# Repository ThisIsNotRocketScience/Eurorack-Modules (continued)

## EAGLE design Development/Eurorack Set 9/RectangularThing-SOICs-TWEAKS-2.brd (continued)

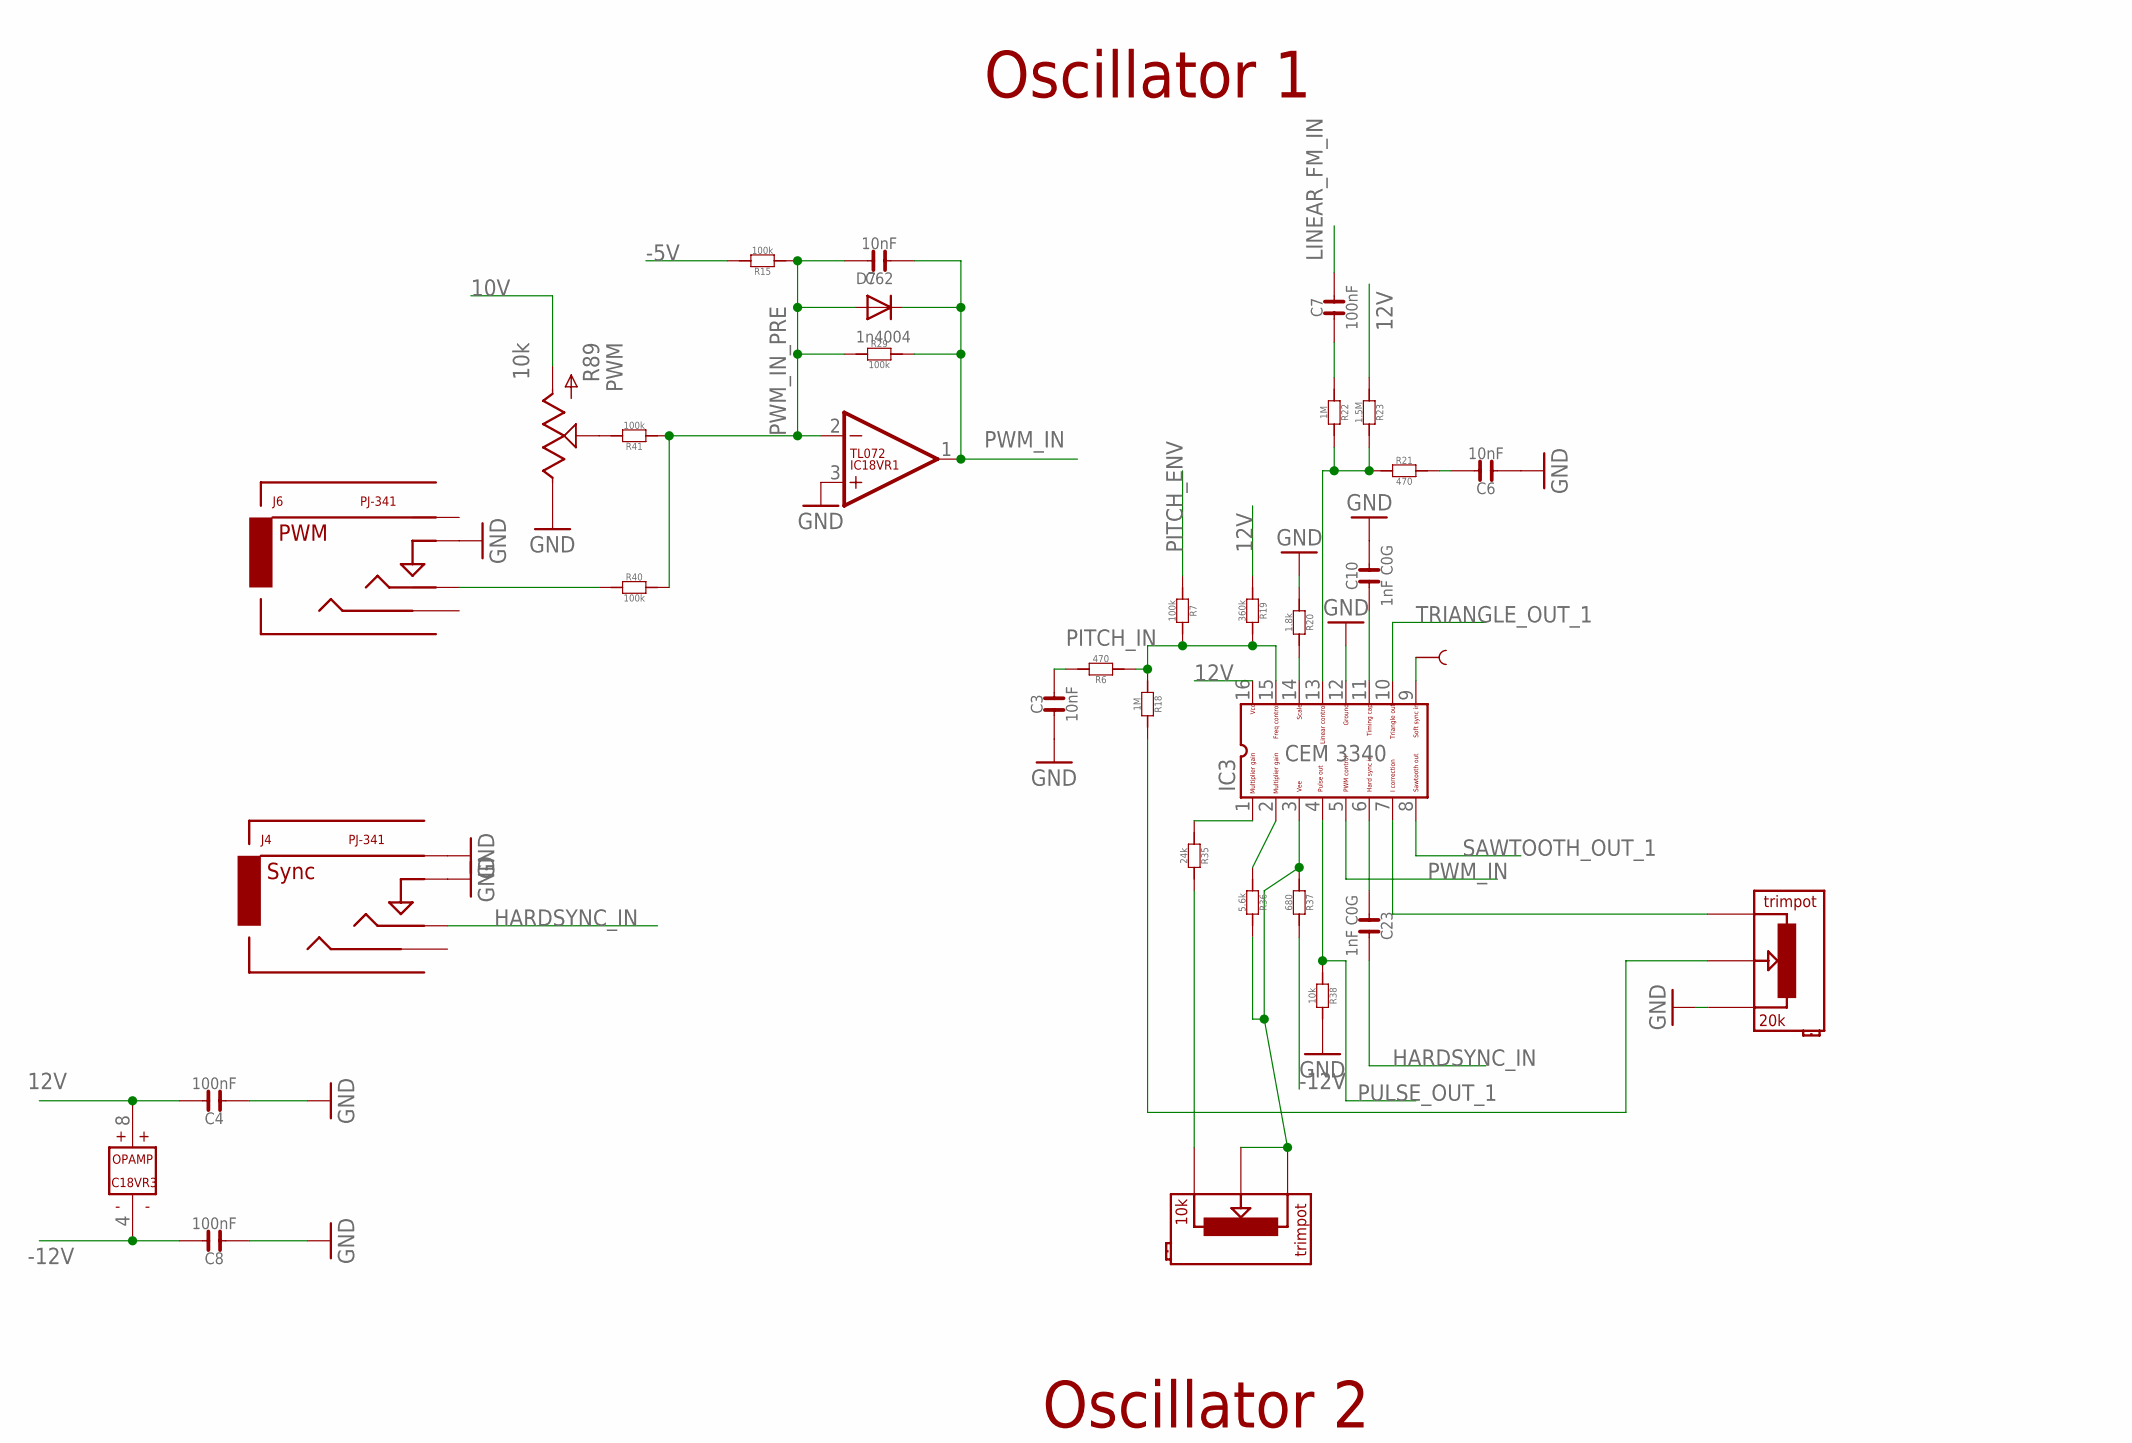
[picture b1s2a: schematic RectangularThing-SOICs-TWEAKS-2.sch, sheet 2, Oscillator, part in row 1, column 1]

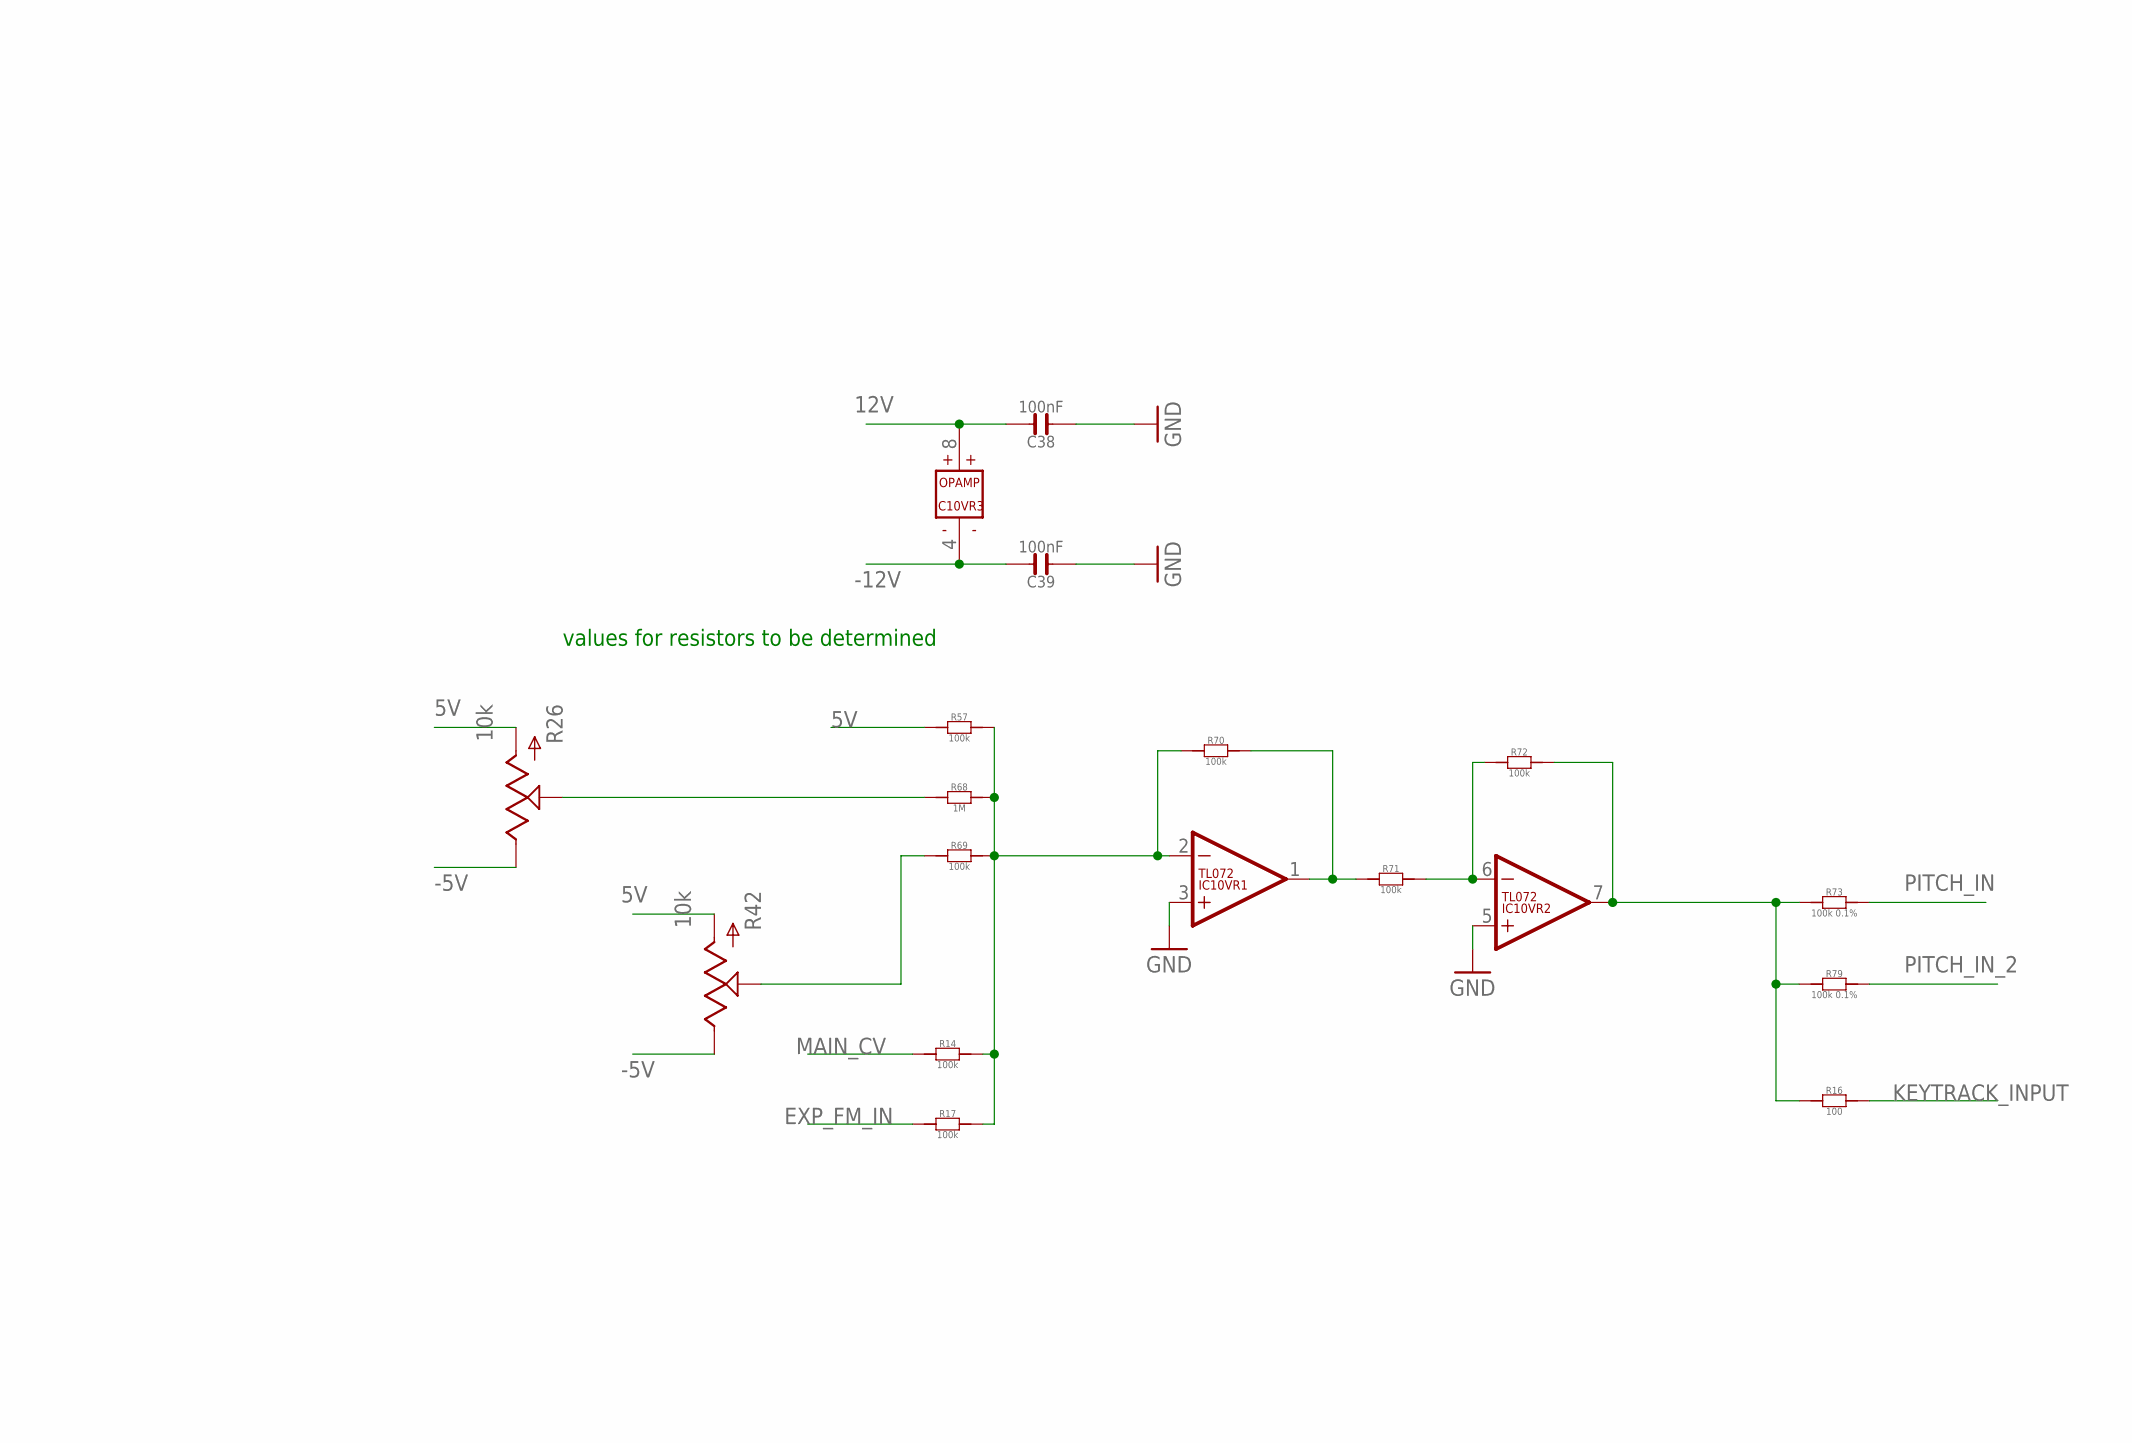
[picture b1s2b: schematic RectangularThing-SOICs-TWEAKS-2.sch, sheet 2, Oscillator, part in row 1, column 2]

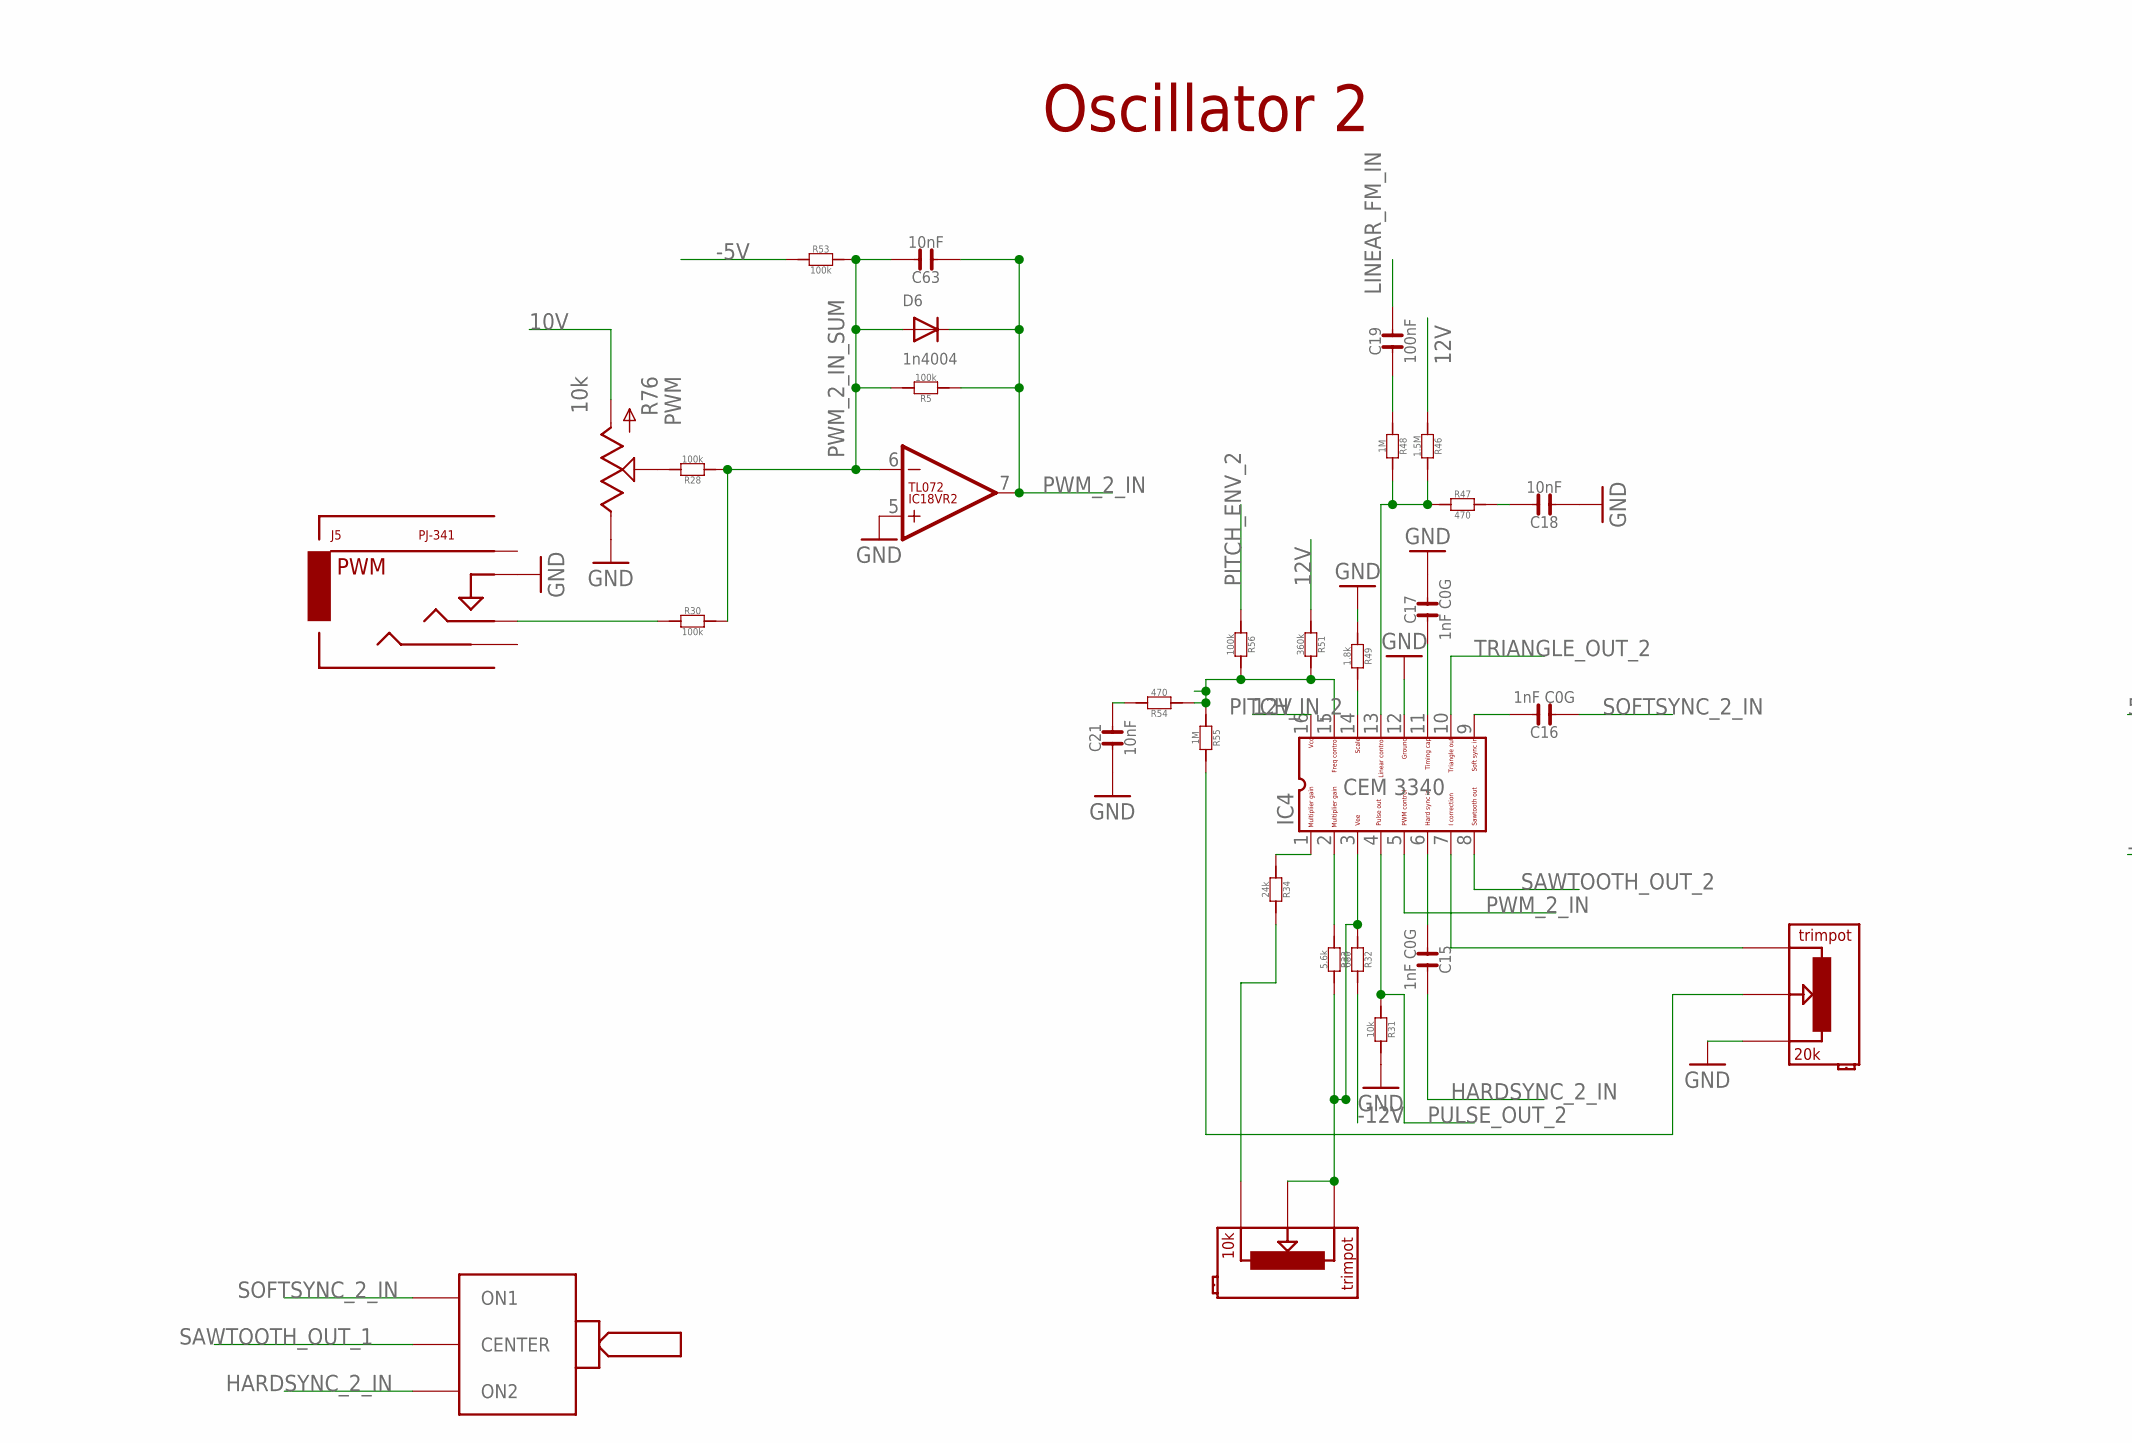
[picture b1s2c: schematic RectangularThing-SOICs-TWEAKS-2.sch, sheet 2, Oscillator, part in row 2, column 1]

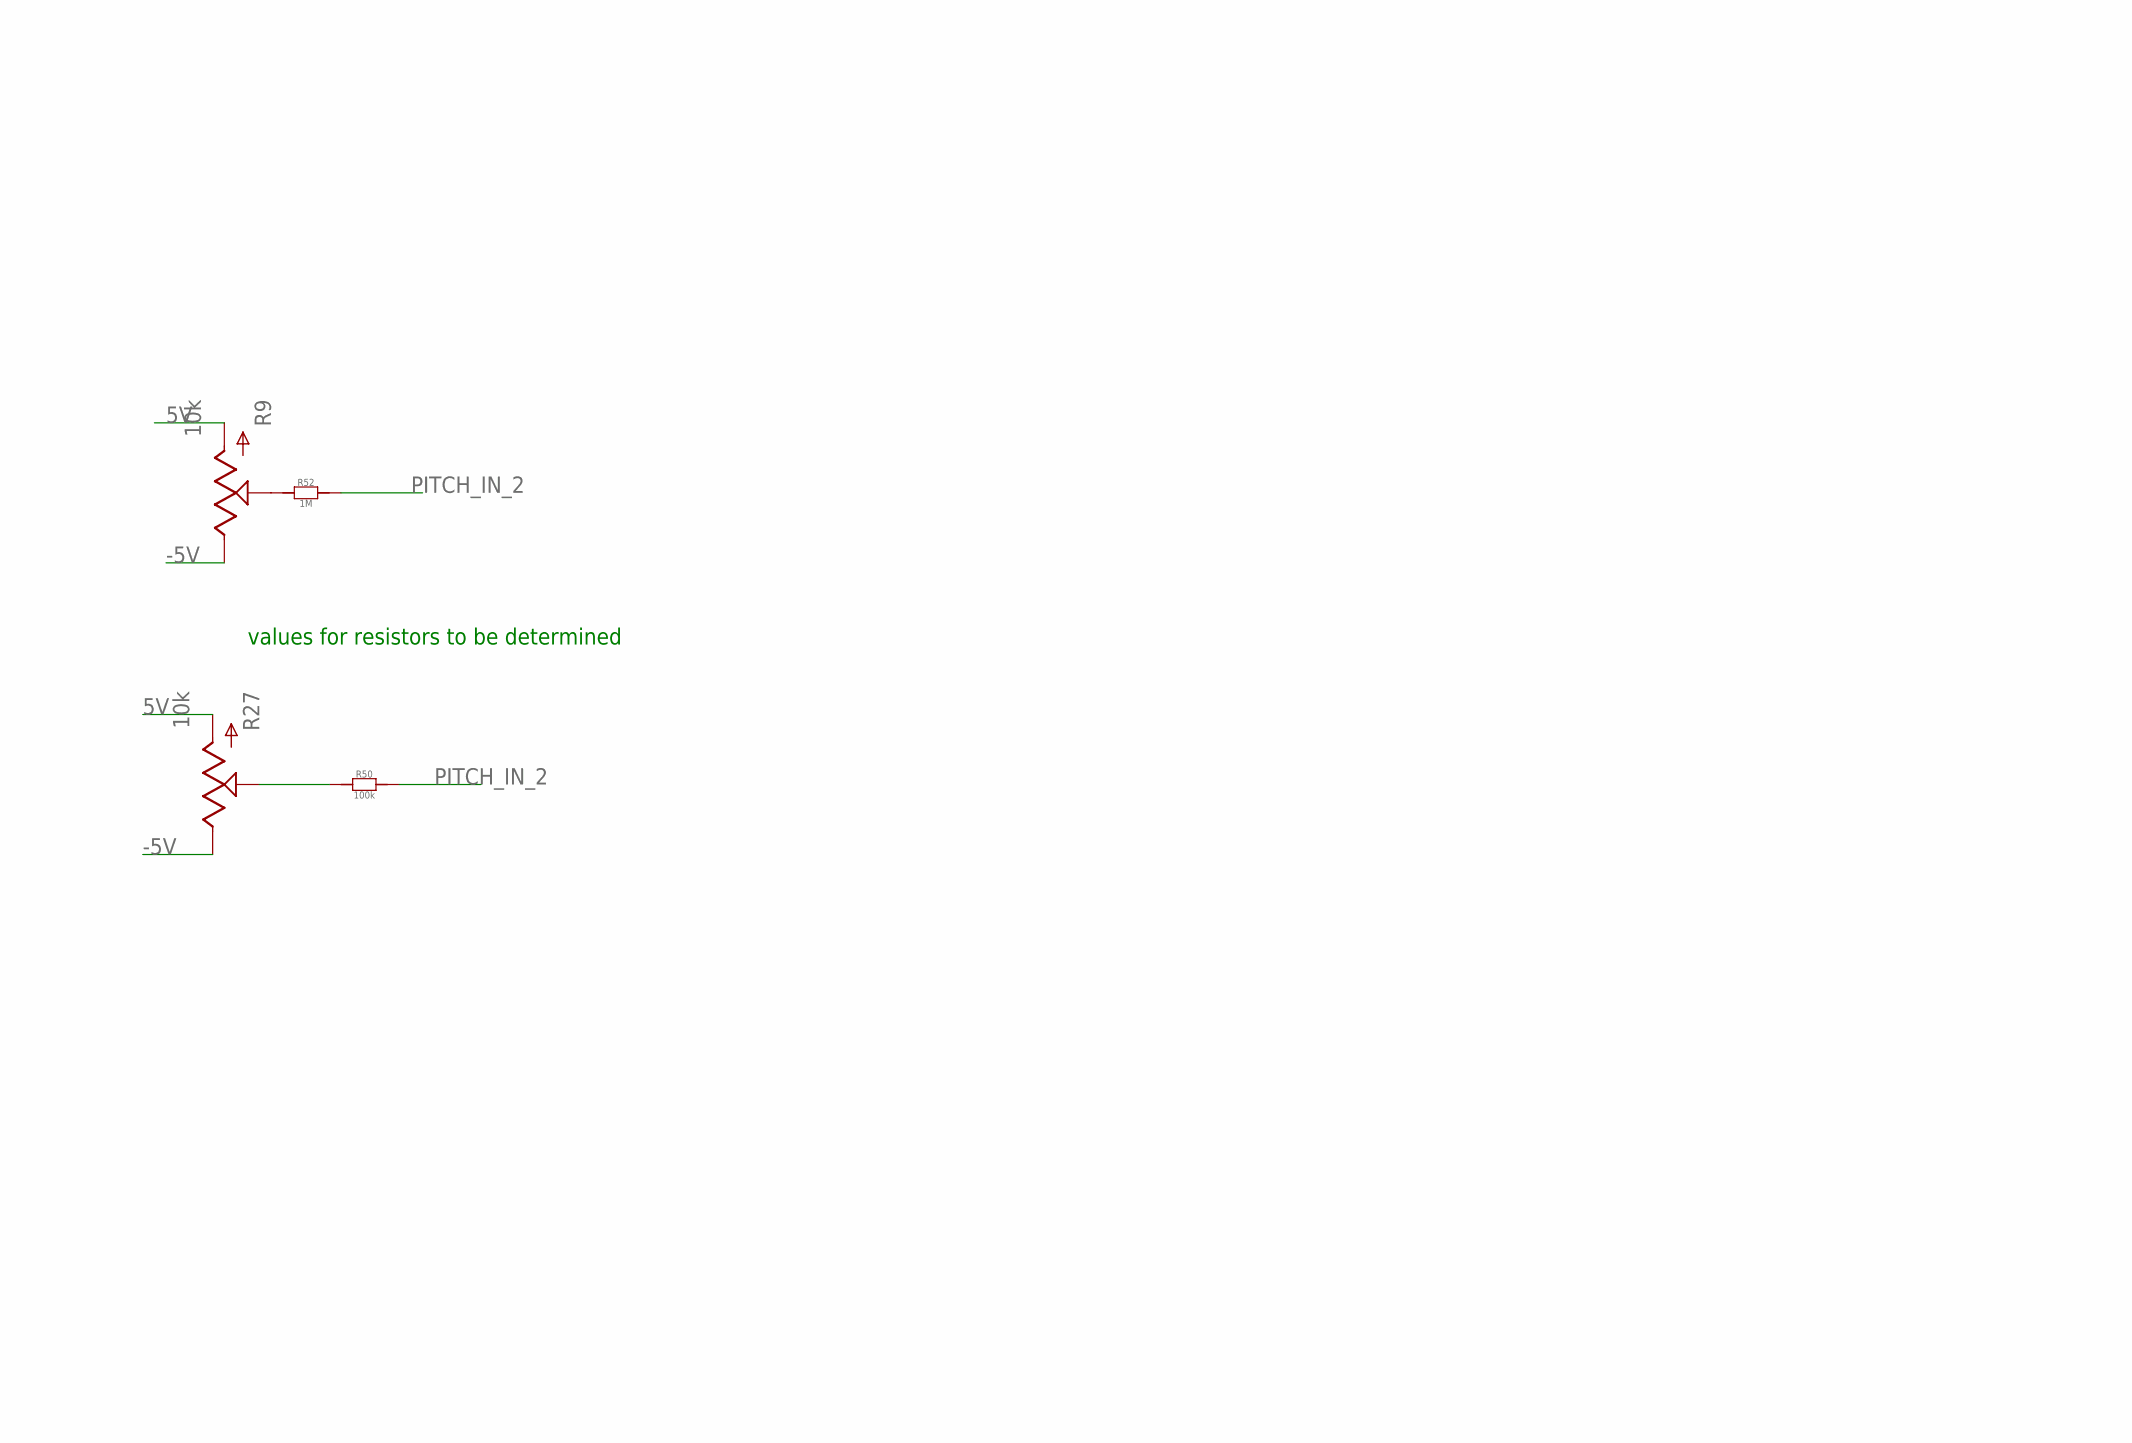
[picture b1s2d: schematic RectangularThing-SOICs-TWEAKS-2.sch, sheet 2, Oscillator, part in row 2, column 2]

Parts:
C3, C6, C18, C21, C62, C63: 10nF; C0603
C4, C7, C8, C19, C38, C39: 100nF; C0603
C10, C15, C16, C17, C23: 1nF C0G; C0603
D6, D7: 1n4004; SOD-323F
IC3, IC4: CEM3340SOIC16; SO16
IC10, IC18: TL072; SO08
J4, J5, J6: PJ-341; 3.5MM-JACK-SWITCH-13MM-INPUT
R5, R7, R14, R15, R17, R28, R29, R30, R40, R41, R50, R53, R56, R57, R69, R70, R71, R72: 100k; R0603
R6, R21, R47, R54: 470; R0603
R9, R26, R27, R42: 10k; OG-POTS_ALPS_POT_VERTICAL_WITHBIGKNOB
R16: 100; R0603
R18, R22, R48, R52, R55, R68: 1M; R0603
R19, R51: 360k; R0603
R20, R49: 1.8k; R0603
R23, R46: 1.5M; R0603
R31, R38: 10k; R0603
R32, R37: 680; R0603
R33, R36: 5.6k; R0603
R34, R35: 24k; R0603
R73, R79: 100k 0.1%; R0603
R76, R89: 10k; OG-POTS_ALPS_POT_VERTICAL
R187, R190: 10k; TRIMPOT
R188, R189: 20k; TRIMPOT
S3: ONOFFON; MULTICOMP1MS-ONOFFON
TP3: TEST-POINT3X5; PAD.03X.05

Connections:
5V: R9.P$3 (A), R26.P$3 (A), R27.P$3 (A), R42.P$3 (A), R57.1; also elsewhere on the board
10V: R76.P$3 (A), R89.P$3 (A); also elsewhere on the board
12V: C4.2, C38.2, IC3.16, IC4.16, IC10.8 (V+), IC18.8 (V+), R19.1, R23.1, R46.1, R51.1; also elsewhere on the board
-5V: R9.P$1 (E), R15.2, R26.P$1 (E), R27.P$1 (E), R42.P$1 (E), R53.1; also elsewhere on the board
-12V: C8.2, C39.2, IC10.4 (V-), IC18.4 (V-), R32.2, R37.2; also elsewhere on the board
EXP_FM_IN: R17.1; also elsewhere on the board
GND: C3.1, C4.1, C6.1, C8.1, C10.2, C17.2, C18.1, C21.1, C38.1, C39.1, IC3.12, IC4.12, IC10.3 (+IN), IC10.5 (+IN), IC18.3 (+IN), IC18.5 (+IN), J4.RING@3 (RING), J4.SWITCH@3 (SWITCH), J5.SWITCH@3 (SWITCH), J6.SWITCH@3 (SWITCH), R20.1, R31.2, R38.2, R49.1, R76.P$1 (E), R89.P$1 (E), R188.P$3, R189.P$3; also elsewhere on the board
HARDSYNC_2_IN: C15.2, S3.3 (ON2)
HARDSYNC_IN: C23.2, J4.TIP@3 (TIP)
INVERTED_CVSUM: IC10.1 (OUT), R70.2, R71.1
KEYTRACK_INPUT: R16.2; also elsewhere on the board
LINEAR_FM_IN: C7.2, C19.2; also elsewhere on the board
MAIN_CV: R14.1; also elsewhere on the board
MAIN_CV_SUMLINE: IC10.2 (-IN), R14.2, R17.2, R57.2, R68.2, R69.2, R70.1
MASTER_COARSEPITCH: R42.P$2 (S), R69.1
MASTER_FINEPITCH: R26.P$2 (S), R68.1
unnamed: C3.2, R6.2
unnamed: C6.2, R21.2
unnamed: IC3.13, R21.1, R22.2, R23.2
unnamed: C7.1, R22.1
unnamed: C10.1, IC3.11
unnamed: IC3.9, TP3.P$1
unnamed: IC3.14, R20.2
unnamed: C23.1, IC3.6
unnamed: IC3.1, R35.1
unnamed: R35.2, R190.P$3
unnamed: IC3.3, R36.2, R37.1, R190.P$1, R190.P$2
unnamed: R18.2, R188.P$2
unnamed: IC3.2, R36.1
unnamed: IC3.7, R188.P$1
unnamed: C21.2, R54.2
unnamed: C18.2, R47.2
unnamed: R41.2, R89.P$2 (S)
unnamed: J6.TIP@3 (TIP), R40.1
unnamed: IC4.13, R46.2, R47.1, R48.2
unnamed: C19.1, R48.1
unnamed: C17.1, IC4.11
unnamed: C16.2, IC4.9
unnamed: IC4.14, R49.2
unnamed: C15.1, IC4.6
unnamed: IC4.1, R34.1
unnamed: R34.2, R187.P$3
unnamed: IC4.3, R32.1, R33.2, R187.P$1, R187.P$2
unnamed: IC4.2, R33.1
unnamed: R55.2, R189.P$2
unnamed: IC4.7, R189.P$1
unnamed: R28.2, R76.P$2 (S)
unnamed: J5.TIP@3 (TIP), R30.1
unnamed: R27.P$2 (S), R50.1
unnamed: R9.P$2 (S), R52.1
PITCH_ENV: R7.1; also elsewhere on the board
PITCH_ENV_2: R56.1; also elsewhere on the board
PITCH_IN: IC3.15, R6.1, R7.2, R18.1, R19.2, R73.2
PITCH_IN_2: IC4.15, R50.2, R51.2, R52.2, R54.1, R55.1, R56.2, R79.2
POSTINVERTED_CVSUM: IC10.6 (-IN), R71.2, R72.1
PRESUMMED_PITCH: IC10.7 (OUT), R16.1, R72.2, R73.1, R79.1
PULSE_OUT_1: IC3.4, R38.1; also elsewhere on the board
PULSE_OUT_2: IC4.4, R31.1; also elsewhere on the board
PWM_2_IN: C63.1, D6.C, IC4.5, IC18.7 (OUT), R5.1
PWM_2_IN_SUM: C63.2, D6.A, IC18.6 (-IN), R5.2, R28.1, R30.2, R53.2
PWM_IN: C62.1, D7.C, IC3.5, IC18.1 (OUT), R29.2
PWM_IN_PRE: C62.2, D7.A, IC18.2 (-IN), R15.1, R29.1, R40.2, R41.1
SAWTOOTH_OUT_1: IC3.8, S3.2 (CENTER); also elsewhere on the board
SAWTOOTH_OUT_2: IC4.8; also elsewhere on the board
SOFTSYNC_2_IN: C16.1, S3.1 (ON1)
TRIANGLE_OUT_1: IC3.10; also elsewhere on the board
TRIANGLE_OUT_2: IC4.10; also elsewhere on the board

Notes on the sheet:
Oscillator 1
values for resistors to be determined
Oscillator 2

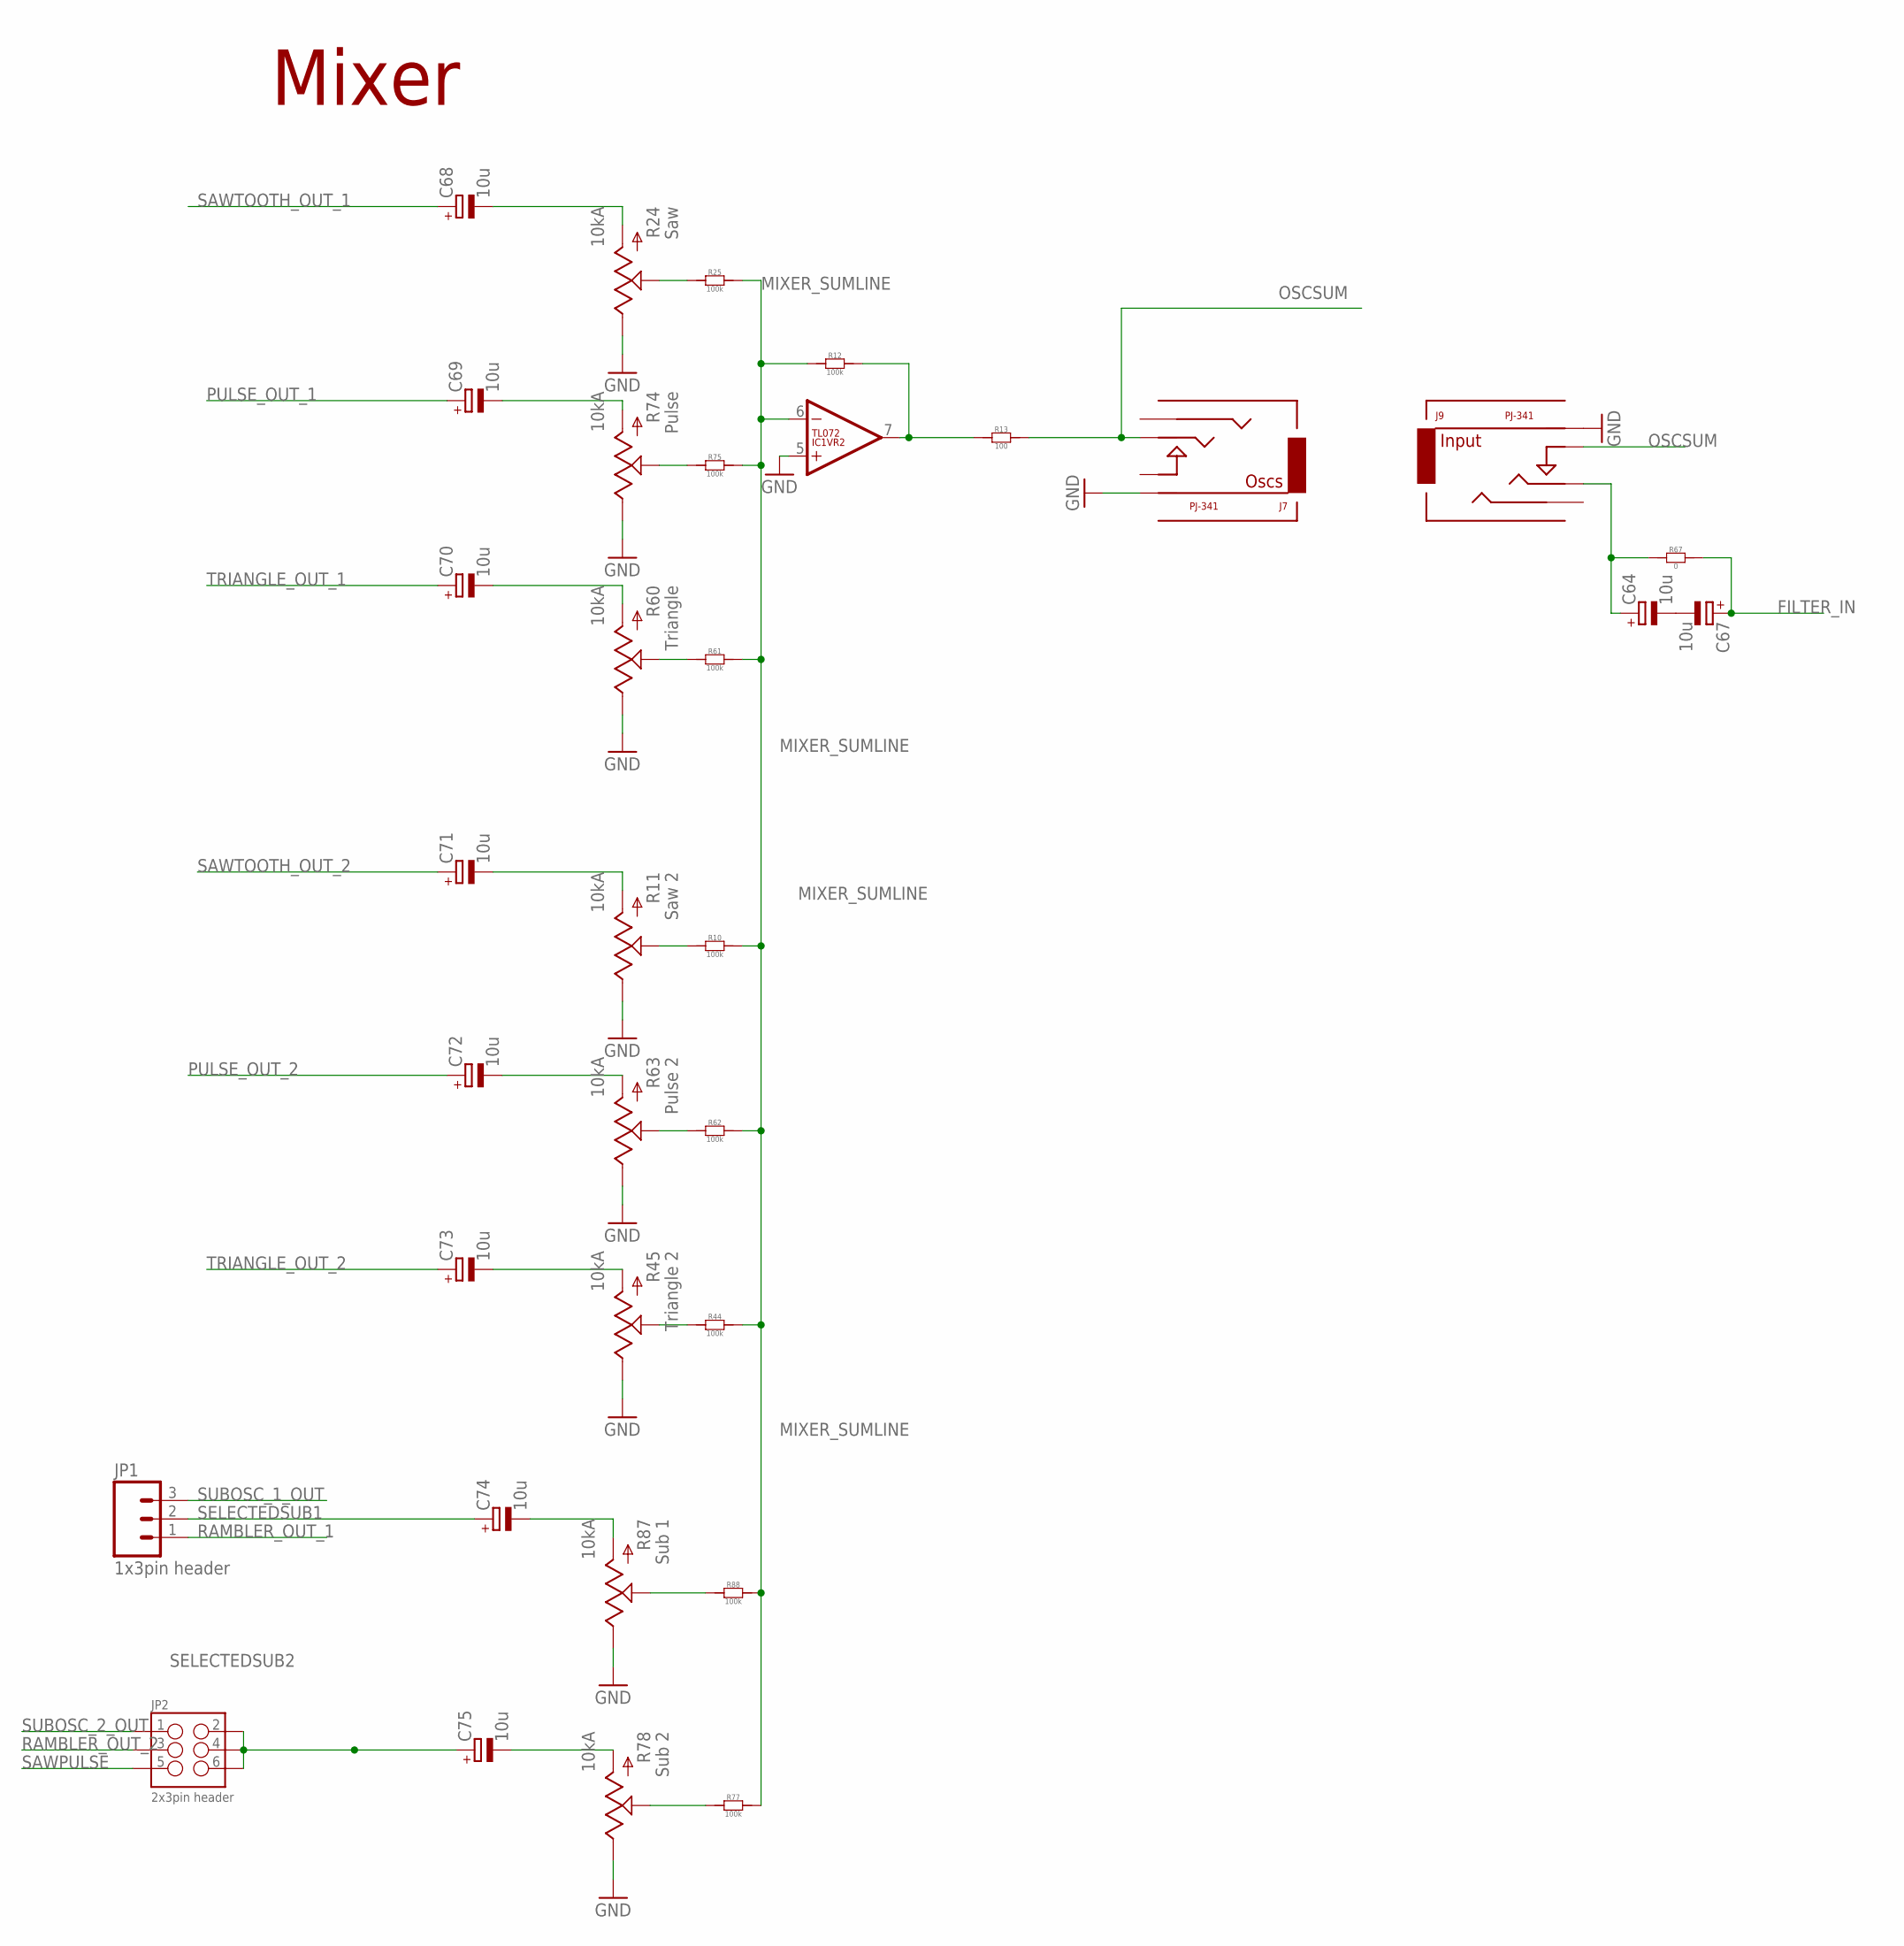
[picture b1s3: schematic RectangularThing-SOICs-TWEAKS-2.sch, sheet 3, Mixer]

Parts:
C64, C67, C68, C69, C70, C71, C72, C73, C74, C75: 10u; CASE_B
IC1: TL072; SO08
J7: PJ-341; 3.5MM-JACK-SWITCH-13MM-OUTPUT
J9: PJ-341; 3.5MM-JACK-SWITCH-13MM-INPUT
JP1: 1x3pin header; 1X03_NO_SILK
JP2: 2x3pin header; 2X3-NS
R10, R12, R25, R44, R61, R62, R75, R77, R88: 100k; R0603
R11, R24, R45, R60, R63, R74, R78, R87: 10kA; OG-POTS_ALPS_POT_VERTICAL
R13: 100; R0603
R67: 0; R0603

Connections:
FILTER_IN: C67.+, R67.2; also elsewhere on the board
GND: IC1.5 (+IN), J7.RING@3 (RING), J9.RING@3 (RING), R11.P$1 (E), R24.P$1 (E), R45.P$1 (E), R60.P$1 (E), R63.P$1 (E), R74.P$1 (E), R78.P$1 (E), R87.P$1 (E); also elsewhere on the board
MIXER_POSTSUM: IC1.7 (OUT), R12.2, R13.1
MIXER_SUMLINE: IC1.6 (-IN), R10.2, R12.1, R25.2, R44.2, R61.2, R62.2, R75.2, R77.2, R88.2
unnamed: R87.P$2 (S), R88.1
unnamed: R60.P$2 (S), R61.1
unnamed: R74.P$2 (S), R75.1
unnamed: R24.P$2 (S), R25.1
unnamed: C68.-, R24.P$3 (A)
unnamed: C69.-, R74.P$3 (A)
unnamed: C70.-, R60.P$3 (A)
unnamed: C64.-, C67.-
unnamed: C71.-, R11.P$3 (A)
unnamed: C72.-, R63.P$3 (A)
unnamed: C73.-, R45.P$3 (A)
unnamed: R44.1, R45.P$2 (S)
unnamed: R62.1, R63.P$2 (S)
unnamed: R10.1, R11.P$2 (S)
unnamed: R77.1, R78.P$2 (S)
unnamed: C74.-, R87.P$3 (A)
unnamed: C75.-, R78.P$3 (A)
OSCSUM: J7.TIP@3 (TIP), J9.SWITCH@3 (SWITCH), R13.2
PREBLOCK_FILTER_IN: C64.+, J9.TIP@3 (TIP), R67.1
PULSE_OUT_1: C69.+; also elsewhere on the board
PULSE_OUT_2: C72.+; also elsewhere on the board
RAMBLER_OUT_1: JP1.1; also elsewhere on the board
RAMBLER_OUT_2: JP2.3; also elsewhere on the board
SAWPULSE: JP2.5; also elsewhere on the board
SAWTOOTH_OUT_1: C68.+; also elsewhere on the board
SAWTOOTH_OUT_2: C71.+; also elsewhere on the board
SELECTEDSUB1: C74.+, JP1.2
SELECTEDSUB2: C75.+, JP2.2, JP2.4, JP2.6
SUBOSC_1_OUT: JP1.3; also elsewhere on the board
SUBOSC_2_OUT: JP2.1; also elsewhere on the board
TRIANGLE_OUT_1: C70.+; also elsewhere on the board
TRIANGLE_OUT_2: C73.+; also elsewhere on the board

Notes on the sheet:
Mixer
